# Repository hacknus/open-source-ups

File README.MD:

# Open Source UPS

[!CAUTION]
The BOOST circuit in rev 2 cannot provide sufficient current to start a HDD.

UPS are commonly used in server applications to protect against power outages. For home applications, for example to protect a NAS, small Uninterruptible Power Supplies (UPS) do exist, but they all lack the USB HID communication to shut down the NAS/Server/Host when the battery gets low.
For small scale applications like Synology NAS products that operate at 12V, there currently exists no UPS product that is able to buffer the power and communicate over USB when the battery level gets critically low.
Only high voltage solutions (110V or 230V) exist, which also include an inverter and are thus much less efficient and overpowered for a simple 12V Synology NAS.
This is a simple, open source UPS, based around an STM32F405 and written in Rust.

The USB HID communication is based on the great work done by [abratchik](https://github.com/abratchik) for the Arduino platform [here](https://github.com/abratchik/HIDPowerDevice/tree/master). 
The hardware is essentially just a charging circuit where the remaining capacity is monitored by the MCU.

## Hardware
Attention! This pcb does not contain a battery protection circuit - if you wish to implement one, just use the Keystone 1047 battery case instead of the Keystone 1048P and wire a breakout 2S BMS before connecting the batteries to the PCB.
The hardware can be found in the [hardware folder](hardware), containing step files for the case as well as EAGLE files for the PCB.

## Flashing the firmware
Easiest way to flash: Connect via USB-C to your computer. Press RESET and BOOT button on the back of the PCB, release RST first and then release BOOT. The device is now in DFU mode.

Then run the following:
```sh
cargo build --release
/usr/bin/arm-none-eabi-objcopy -O binary   target/thumbv7em-none-eabihf/release/open-source-ups   firmware.bin
dfu-util -l
dfu-util -d 0483:df11 -a 0 \
  -s 0x08000000:leave -D firmware.bin
```

Alternatively:
Connect the board using a ST-Link V3 (with TagConnect) to a USB port on the computer. Be sure to power the board with an
additional USB-C connector. (ST-Link does not provide power)  
First start the openocd server in a terminal/console window:
```openocd -f interface/stlink-v2-1.cfg -f target/stm32f4x.cfg```   
Flash/Run the code on the hardware using:  
```cargo run --release```  
note: release is important for USB to work reliably!

To set up your system, be sure to
follow [this guide](https://docs.rust-embedded.org/discovery/f3discovery/03-setup/index.html)!

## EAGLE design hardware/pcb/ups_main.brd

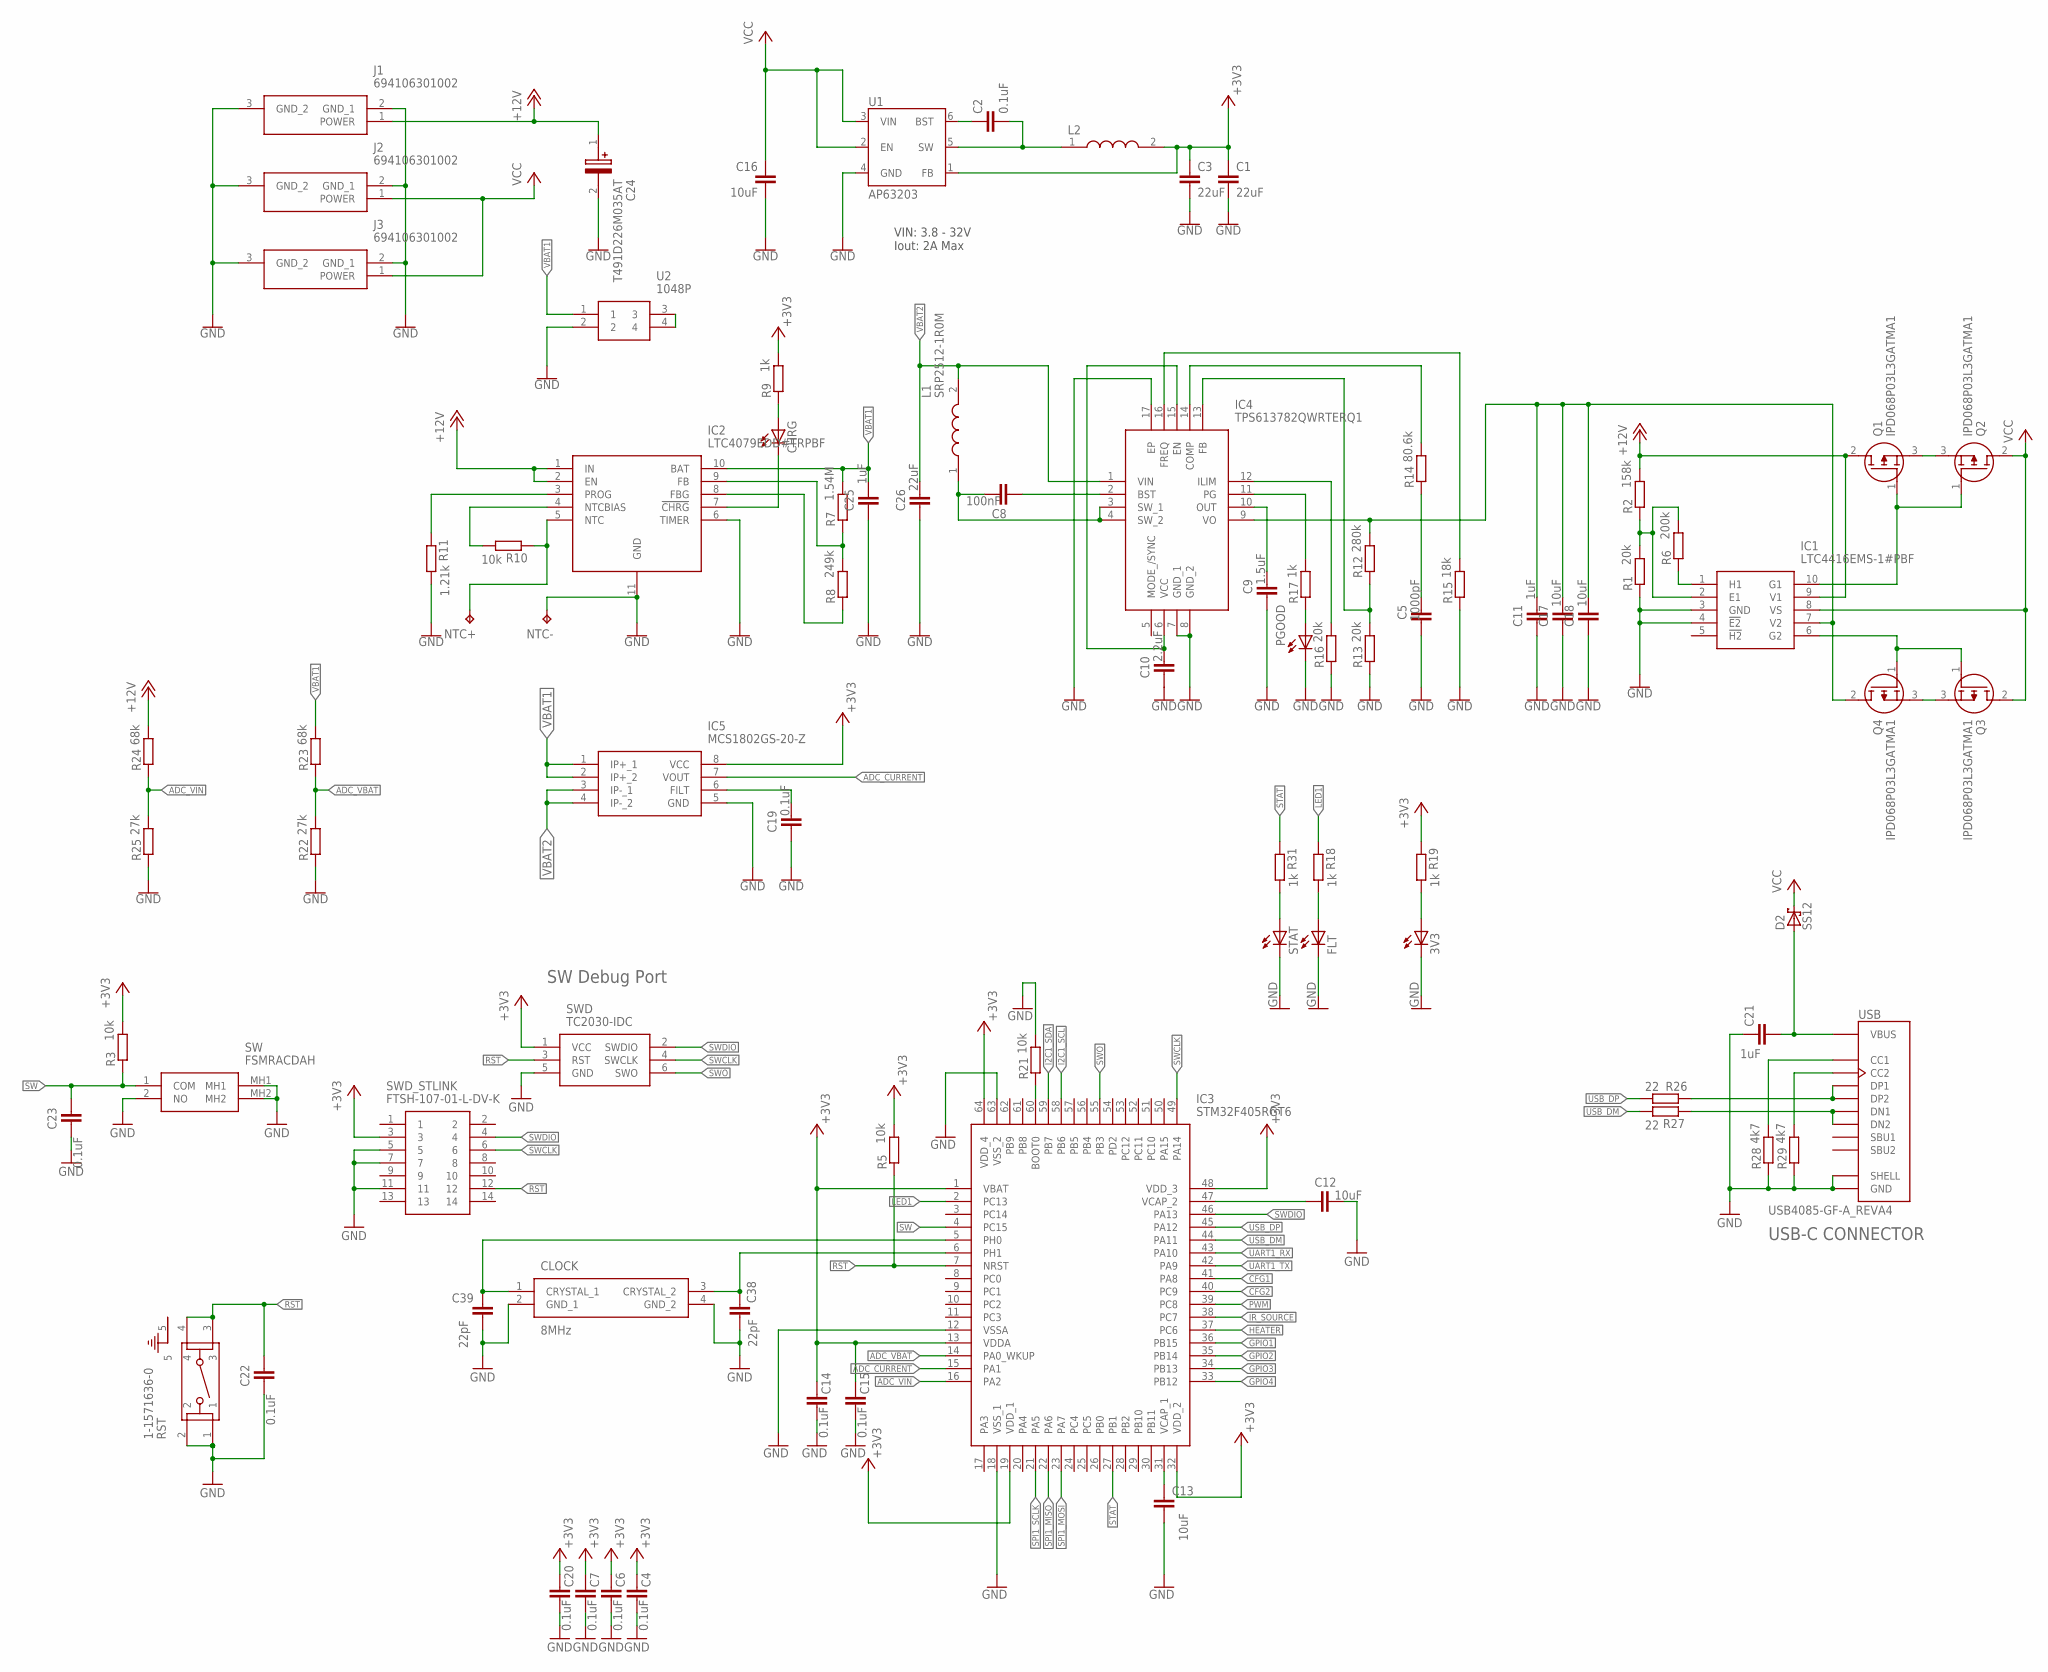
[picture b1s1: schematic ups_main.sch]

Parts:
3V3: LEDCHIPLED_0805; CHIPLED_0805
C1, C3: 22uF; 0603
C2: 0.1uF; 0603
C4, C6, C7, C14, C15, C19, C20, C22, C23: 0.1uF; C0603K
C5: 1000pF; C0603K
C8: 100nF; C0603K
C9: 1.5uF; C0603K
C10: 2.2uF; C0603K
C11, C21, C25: 1uF; C0603K
C12, C13, C17, C18: 10uF; C0603K
C16: 10uF; 1210
C24: T491D226M035AT; T491D
C26: 22uF; C0603K
C38, C39: 22pF; C0603K
CHRG: LEDCHIPLED_0805; CHIPLED_0805
CLOCK: 8MHz; ABM8AIG8000MHZ1ZT
D2: SS12; DO214AC
FLT: LEDCHIPLED_0805; CHIPLED_0805
IC1: LTC4416EMS-1#PBF; SOP50P490X110-10N
IC2: LTC4079EDD#TRPBF; SON50P300X300X80-11N
IC3: STM32F405RGT6; QFP50P1200X1200X160-64N
IC4: TPS613782QWRTERQ1; QFN50P300X300X80-17N
IC5: MCS1802GS-20-Z; SOIC127P600X175-8N
J1, J2, J3: 694106301002; 694106301002_1
L1: SRP2512-1R0M; INDC2520X120N
L2: MLZ2012M4R7HT000; INDC2012X145N
NTC+: TPPAD1-17; P1-17
NTC-: TPPAD1-17; P1-17
PGOOD: LEDCHIPLED_0805; CHIPLED_0805
Q1, Q2, Q3, Q4: IPD068P03L3GATMA1
R1, R13, R16: 20k; R0603
R2: 158k; R0603
R3, R5, R10, R21: 10k; R0603
R6: 200k; R0603
R7: 1.54M; R0603
R8: 249k; R0603
R9, R17, R18, R19, R31: 1k; R0603
R11: 1.21k; R0603
R12: 280k; R0603
R14: 80.6k; R0603
R15: 18k; R0603
R22, R25: 27k; R0603
R23, R24: 68k; R0603
R26, R27: 22; R0603
R28, R29: 4k7; R0603
RST: 1-1571636-0; SW5_1571636
STAT: LEDCHIPLED_0805; CHIPLED_0805
SW: FSMRACDAH
SWD: TC2030-IDC; TC2030IDC
SWD_STLINK: FTSH-107-01-L-DV-K; FTSH-107-XX-YYY-DV-K
U1: AP63203; SOT23-6
U2: 1048P
USB: USB4085-GF-A_REVA4; GCT_USB4085-GF-A_REVA4

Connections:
+3V3: C1.1, C3.1, C4.1, C6.1, C7.1, C14.1, C15.1, C20.1, IC3.1 (VBAT), IC3.13 (VDDA), IC3.19 (VDD_1), IC3.32 (VDD_2), IC3.48 (VDD_3), IC3.64 (VDD_4), IC5.8 (VCC), L2.2, R3.2, R5.2, R9.2, R19.1, SWD.1 (VCC), SWD_STLINK.3, U1.1 (FB)
+12V: C24.1 (+), IC1.9 (V1), IC2.1 (IN), IC2.2 (EN), J1.1 (POWER), Q1.2 (D), R2.2, R24.2
ADC_CURRENT: IC3.15 (PA1), IC5.7 (VOUT)
ADC_VBAT: IC3.14 (PA0_WKUP), R22.2, R23.1
ADC_VIN: IC3.16 (PA2), R24.1, R25.2
CFG1: IC3.41 (PA8)
CFG2: IC3.40 (PC9)
GND: 3V3.C, C1.2, C3.2, C4.2, C5.1, C6.2, C7.2, C9.1, C10.1, C11.1, C12.2, C13.2, C14.2, C15.2, C16.2, C17.1, C18.1, C19.1, C20.2, C21.1, C22.2, C23.2, C24.2 (-), C25.1, C26.1, C38.2, C39.2, CLOCK.2 (GND_1), CLOCK.4 (GND_2), FLT.C, IC1.3 (GND), IC1.4 (!E2), IC2.6 (TIMER), IC2.11 (GND), IC3.12 (VSSA), IC3.18 (VSS_1), IC3.63 (VSS_2), IC4.7 (GND_1), IC4.8 (GND_2), IC4.17 (EP), IC5.5 (GND), J1.2 (GND_1), J1.3 (GND_2), J2.2 (GND_1), J2.3 (GND_2), J3.2 (GND_1), J3.3 (GND_2), NTC-.TP, PGOOD.C, R1.1, R11.2, R13.1, R15.1, R16.1, R21.2, R22.1, R25.1, R28.1, R29.1, RST.1, RST.2, STAT.C, SW.2 (NO), SW.MH1, SW.MH2, SWD.5 (GND), SWD_STLINK.5, SWD_STLINK.7, SWD_STLINK.11, U1.4 (GND), U2.2, USB.A1 (GND), USB.A12 (GND), USB.B1 (GND), USB.B12 (GND), USB.P1 (SHELL), USB.P2 (SHELL), USB.P3 (SHELL), USB.P4 (SHELL)
GPIO1: IC3.36 (PB15)
GPIO2: IC3.35 (PB14)
GPIO3: IC3.34 (PB13)
GPIO4: IC3.33 (PB12)
HEATER: IC3.37 (PC6)
I2C1_SCL: IC3.58 (PB6)
I2C1_SDA: IC3.59 (PB7)
IR_SOURCE: IC3.38 (PC7)
LED1: IC3.2 (PC13), R18.1
unnamed: C2.1, U1.6 (BST)
unnamed: Q3.3 (S), Q4.3 (S)
unnamed: IC1.6 (G2), Q3.1 (G), Q4.1 (G)
unnamed: FLT.A, R18.2
unnamed: IC1.10 (G1), Q1.1 (G), Q2.1 (G)
unnamed: C12.1, IC3.47 (VCAP_2)
unnamed: IC1.1 (H1), R6.1
unnamed: IC1.2 (E1), R1.2, R2.1, R6.2
unnamed: C2.2, L2.1, U1.5 (SW)
unnamed: Q1.3 (S), Q2.3 (S)
unnamed: IC4.12 (ILIM), R16.2
unnamed: C13.1, IC3.31 (VCAP_1)
unnamed: IC4.11 (PG), R17.2
unnamed: IC2.4 (NTCBIAS), R10.2
unnamed: IC2.5 (NTC), NTC+.TP, R10.1
unnamed: IC2.3 (PROG), R11.1
unnamed: IC2.9 (FB), R7.1, R8.2
unnamed: IC2.8 (FBG), R8.1
unnamed: CHRG.C, IC2.7 (!CHRG)
unnamed: C38.1, CLOCK.3 (CRYSTAL_2), IC3.6 (PH1)
unnamed: C9.2, IC4.10 (OUT)
unnamed: IC4.16 (FREQ), R15.2
unnamed: IC4.14 (COMP), R14.2
unnamed: C8.1, IC4.2 (BST)
unnamed: C8.2, IC4.3 (SW_1), IC4.4 (SW_2), L1.1
unnamed: C39.1, CLOCK.1 (CRYSTAL_1), IC3.5 (PH0)
unnamed: C5.2, R14.1
unnamed: IC4.13 (FB), R12.1, R13.2
unnamed: 3V3.A, R19.2
unnamed: R31.2, STAT.A
unnamed: C21.2, D2.A, USB.A4 (VBUS), USB.A9 (VBUS), USB.B4 (VBUS), USB.B9 (VBUS)
unnamed: PGOOD.A, R17.1
unnamed: CHRG.A, R9.1
unnamed: IC3.60 (BOOT0), R21.1
unnamed: R26.1, USB.A6 (DP1), USB.B6 (DP2)
unnamed: C10.2, IC4.6 (VCC), IC4.15 (EN)
unnamed: R27.1, USB.A7 (DN1), USB.B7 (DN2)
unnamed: C19.2, IC5.6 (FILT)
unnamed: U2.3, U2.4
unnamed: R29.2, USB.B5 (CC2)
unnamed: R28.2, USB.A5 (CC1)
PWM: IC3.39 (PC8)
RST: C22.1, IC3.7 (NRST), R5.1, RST.3, RST.4, SWD.3 (RST), SWD_STLINK.12
SPI1_MISO: IC3.22 (PA6)
SPI1_MOSI: IC3.23 (PA7)
SPI1_SCLK: IC3.21 (PA5)
STAT: IC3.27 (PB1), R31.1
SW: C23.1, IC3.4 (PC15), R3.1, SW.1 (COM)
SWCLK: IC3.49 (PA14), SWD.4 (SWCLK), SWD_STLINK.6
SWDIO: IC3.46 (PA13), SWD.2 (SWDIO), SWD_STLINK.4
SWO: IC3.55 (PB3), SWD.6 (SWO)
UART1_RX: IC3.43 (PA10)
UART1_TX: IC3.42 (PA9)
USB_DM: IC3.44 (PA11), R27.2
USB_DP: IC3.45 (PA12), R26.2
VBAT1: C25.2, IC2.10 (BAT), IC5.1 (IP+_1), IC5.2 (IP+_2), R7.2, R23.2, U2.1
VBAT2: C26.2, IC4.1 (VIN), IC5.3 (IP-_1), IC5.4 (IP-_2), L1.2
VCC: C16.1, D2.C, IC1.8 (VS), J2.1 (POWER), J3.1 (POWER), Q2.2 (D), Q3.2 (D), U1.2 (EN), U1.3 (VIN)
VO: C11.2, C17.2, C18.2, IC1.7 (V2), IC4.9 (VO), Q4.2 (D), R12.2

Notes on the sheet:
SW Debug Port
VIN: 3.8 - 32V Iout: 2A Max
USB-C CONNECTOR

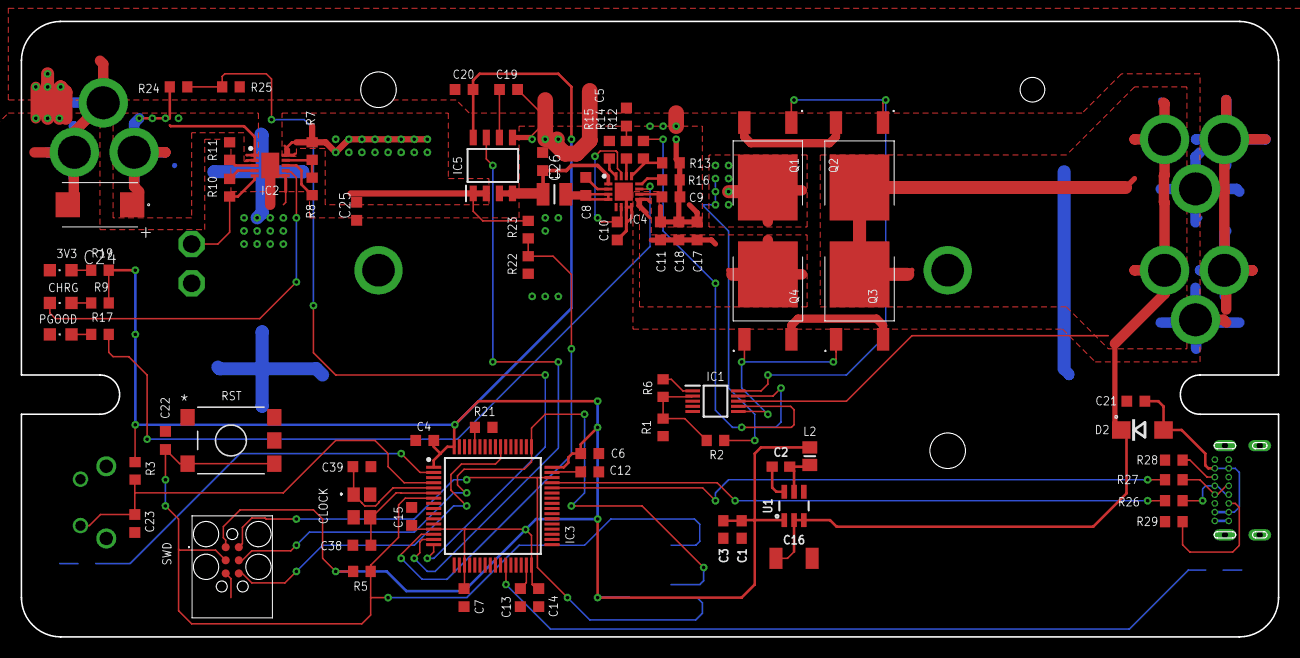
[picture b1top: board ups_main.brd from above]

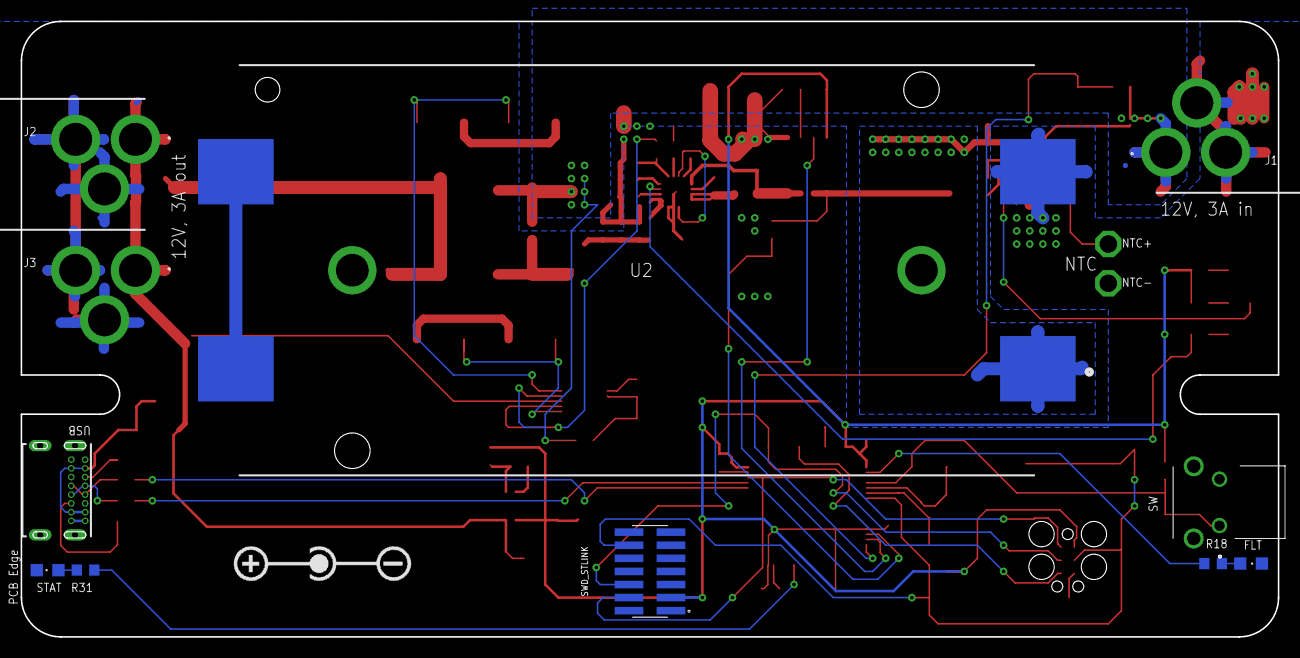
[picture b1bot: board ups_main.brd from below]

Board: 2 copper layers, 121.9 x 59.7 mm, 86 parts (11 on the bottom side), 60 nets.

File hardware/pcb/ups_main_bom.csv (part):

Qty,Value,Device,Package,Parts,Description,ARROW_PART_NUMBER,ARROW_PRICE-STOCK,AVAILABILITY,BUILT_BY,CONFIGURATION__POLE-THROW_,COPYRIGHT,DESCRIPTION,HEIGHT,MANUFACTURER_NAME,MANUFACTURER_PART_NUMBER,MAX_SWITCHING_CURRENT,MAX_SWITCHING_VOLTAGE_AC_,MF,MOUSER_PART_NUMBER,MOUSER_PRICE-STOCK,MP,PACKAGE,POPULARITY,PRICE,PRODUCT_TYPE,PROD_ID,PURCHASE-URL,RS_PART_NUMBER,RS_PRICE-STOCK,SPICEPREFIX,SWITCH_TYPE,TE_PART_NUMBER,TP_SIGNAL_NAME,VALUE,VENDOR,
5,,LEDCHIPLED_0805,CHIPLED_0805,"3V3, CHRG, FLT, PGOOD, STAT",LED,,,,,,,,,,,,,,,,,,,,,,,,,,,,,,,
1,0.1uF,0.1UF-0603-25V-5%,603,C2,0.1µF ceramic capacitors,,,,,,,,,,,,,,,,,,,,,CAP-08604,,,,,,,,0.1uF,,
9,0.1uF,C-EUC0603K,C0603K,"C4, C6, C7, C14, C15, C19, C20, C22, C23","CAPACITOR, European symbol",,,,,,,,,,,,,,,,,,30,,,,,,,C,,,,,,
1,1-1571636-0,1-1571636-0,SW5_1571636,RST,,,,,EMA_UL_Team,Single Pole - Single Throw,Copyright (C) 2016 Accelerated Designs. All rights reserved,"TACT,SMT,GULL WING,260GF,T&R",,,1-1571636-0,-,-,,,,,,,,Switch,,,,,,Tactile Switches,1-1571636-0,,,TE Connectivity,
1,1.21k,R-EU_R0603,R0603,R11,"RESISTOR, European symbol",,,,,,,,,,,,,,,,,,70,,,,,,,R,,,,,,
1,1.54M,R-EU_R0603,R0603,R7,"RESISTOR, European symbol",,,,,,,,,,,,,,,,,,70,,,,,,,R,,,,,,
1,1.5uF,C-EUC0603K,C0603K,C9,"CAPACITOR, European symbol",,,,,,,,,,,,,,,,,,30,,,,,,,C,,,,,,
1,1000pF,C-EUC0603K,C0603K,C5,"CAPACITOR, European symbol",,,,,,,,,,,,,,,,,,30,,,,,,,C,,,,,,
1,100nF,C-EUC0603K,C0603K,C8,"CAPACITOR, European symbol",,,,,,,,,,,,,,,,,,30,,,,,,,C,,,,,,
1,1048P,1048P,1048P,U2,"KEYSTONE - 1048P - BATTERY HOLDER, 18650, SMD",,,,,,,"KEYSTONE - 1048P - BATTERY HOLDER, 18650, SMD",mm,Keystone Electronics,1048P,,,,534-1048P,https://www.mouser.co.uk/ProductDetail/Keystone-Electronics/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,,,,,,,,,,,,,,,,
4,10k,R-EU_R0603,R0603,"R3, R5, R10, R21","RESISTOR, European symbol",,,,,,,,,,,,,,,,,,70,,,,,,,R,,,,,,
1,10uF,10UF-1210-50V-20%,1210,C16,10.0µF ceramic capacitors,,,,,,,,,,,,,,,,,,,,,CAP-09824,,,,,,,,10uF,,
4,10uF,C-EUC0603K,C0603K,"C12, C13, C17, C18","CAPACITOR, European symbol",,,,,,,,,,,,,,,,,,30,,,,,,,C,,,,,,
1,158k,R-EU_R0603,R0603,R2,"RESISTOR, European symbol",,,,,,,,,,,,,,,,,,70,,,,,,,R,,,,,,
1,18k,R-EU_R0603,R0603,R15,"RESISTOR, European symbol",,,,,,,,,,,,,,,,,,70,,,,,,,R,,,,,,
5,1k,R-EU_R0603,R0603,"R9, R17, R18, R19, R31","RESISTOR, European symbol",,,,,,,,,,,,,,,,,,70,,,,,,,R,,,,,,
3,1uF,C-EUC0603K,C0603K,"C11, C21, C25","CAPACITOR, European symbol",,,,,,,,,,,,,,,,,,30,,,,,,,C,,,,,,
1,2.2uF,C-EUC0603K,C0603K,C10,"CAPACITOR, European symbol",,,,,,,,,,,,,,,,,,30,,,,,,,C,,,,,,
1,200k,R-EU_R0603,R0603,R6,"RESISTOR, European symbol",,,,,,,,,,,,,,,,,,70,,,,,,,R,,,,,,
3,20k,R-EU_R0603,R0603,"R1, R13, R16","RESISTOR, European symbol",,,,,,,,,,,,,,,,,,70,,,,,,,R,,,,,,
2,22,R-EU_R0603,R0603,"R26, R27","RESISTOR, European symbol",,,,,,,,,,,,,,,,,,70,,,,,,,R,,,,,,
2,22pF,C-EUC0603K,C0603K,"C38, C39","CAPACITOR, European symbol",,,,,,,,,,,,,,,,,,30,,,,,,,C,,,,,,
2,22uF,22UF-0603-6.3V-20%,603,"C1, C3",22µF ceramic capacitors,,,,,,,,,,,,,,,,,,,,,CAP-14464,,,,,,,,22uF,,
1,22uF,C-EUC0603K,C0603K,C26,"CAPACITOR, European symbol",,,,,,,,,,,,,,,,,,30,,,,,,,C,,,,,,
1,249k,R-EU_R0603,R0603,R8,"RESISTOR, European symbol",,,,,,,,,,,,,,,,,,70,,,,,,,R,,,,,,
2,27k,R-EU_R0603,R0603,"R22, R25","RESISTOR, European symbol",,,,,,,,,,,,,,,,,,70,,,,,,,R,,,,,,
1,280k,R-EU_R0603,R0603,R12,"RESISTOR, European symbol",,,,,,,,,,,,,,,,,,70,,,,,,,R,,,,,,
2,4k7,R-EU_R0603,R0603,"R28, R29","RESISTOR, European symbol",,,,,,,,,,,,,,,,,,70,,,,,,,R,,,,,,
2,68k,R-EU_R0603,R0603,"R23, R24","RESISTOR, European symbol",,,,,,,,,,,,,,,,,,70,,,,,,,R,,,,,,
3,694106301002,694106301002,694106301002_1,"J1, J2, J3","WURTH ELEKTRONIK - 694106301002 - CONNECTOR, POWER ENTRY, JACK, 3A, 20VDC",,,,,,,"WURTH ELEKTRONIK - 694106301002 - CONNECTOR, POWER ENTRY, JACK, 3A, 20VDC",mm,Wurth Elektronik,694106301002,,,,710-694106301002,https://www.mouser.co.uk/ProductDetail/Wurth-Elektronik/6941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,,,,,,,,,,,,,,,,
1,80.6k,R-EU_R0603,R0603,R14,"RESISTOR, European symbol",,,,,,,,,,,,,,,,,,70,,,,,,,R,,,,,,
1,8MHz,ABM8AIG-8.000MHZ-1Z-T,ABM8AIG8000MHZ1ZT,CLOCK,Crystals 18pF 8MHz 10ppm AEC-Q200 -40C +125C,,,,,,,Crystals 18pF 8MHz 10ppm AEC-Q200 -40C +125C,0.8mm,ABRACON,ABM8AIG-8.000MHZ-1Z-T,,,,815-M8AIG-8-1ZT,https://www.mouser.com/Search/Refine.aspx?Keyword=815-M8AIG-8-1ZT,,,,,,,,,,,,,,,,
1,AP63203,AP63203,SOT23-6,U1,Diodes Inc. AP63203 3.8V-32V input 3.3V Buck,,,,,,,,,,,,,,,,,,,,,VREG-15244,,,,,,,,AP63203,,
1,FSMRACDAH,FSMRACDAH,FSMRACDAH,SW,"TE CONNECTIVITY / ALCOSWITCH - FSMRACDAH - TACTILE SWITCH, SPST-NO, 0.05A, 24V, TH",,,,,,,"TE CONNECTIVITY / ALCOSWITCH - FSMRACDAH - TACTILE SWITCH, SPST-NO, 0.05A, 24V, TH",9.2mm,TE Connectivity,FSMRACDAH,,,,506-FSMRACDAH,https://www.mouser.co.uk/ProductDetail/TE-Connectivity-Alcos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,,,,,,,,,,,,,,,,
1,FTSH-107-01-L-DV-K,FTSH-107-01-L-DV-K,FTSH-107-XX-YYY-DV-K,SWD_STLINK,"14 Position, High Reliability Header Strips, 0.050 pitch""",FTSH-107-01-L-DV-K,https://www.arrow.com/en/products/ftsh-107-01-l-dv-k/samtec,,,,,"14 Position, High Reliability Header Strips, 0.050&quot", pitch,mm,SAMTEC,FTSH-107-01-L-DV-K,,,,200-FTSH10701LDVK,https://www.mouser.co.uk/ProductDetail/Samtec/FTSH-107-01-L-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,,,,,,,,,,,,,,,
4,IPD068P03L3GATMA1,IPD068P03L3GATMA1,IPD068P03L3GATMA1,"Q1, Q2, Q3, Q4",MOSFET TRENCH,,,,,,,MOSFET TRENCH <= 40V,2.41mm,Infineon,IPD068P03L3GATMA1,,,,726-IPD068P03L3GATMA,https://www.mouser.co.uk/ProductDetail/Infineon-Technologies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,,,,,,,,,,,,,,,,
1,LTC4079EDD#TRPBF,LTC4079EDD#TRPBF,SON50P300X300X80-11N,IC2,"Battery Management Low Iq 60V, 250mA Linear Charger",,,,,,,"Battery Management Low Iq 60V, 250mA Linear Charger",0.8mm,Analog Devices,LTC4079EDD#TRPBF,,,,584-LTC4079EDD#TRPBF,https://www.mouser.co.uk/ProductDetail/Analog-Devices/LTC407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,,,,,,,,,,,,,,,,
1,LTC4416EMS-1#PBF,LTC4416EMS-1#PBF,SOP50P490X110-10N,IC1,"Linear Technology LTC4416EMS-1#PBF, MOSFET Controller 10-Pin, MSOP",,,,,,,"Linear Technology LTC4416EMS-1#PBF, MOSFET Controller 10-Pin, MSOP",1.1mm,Analog Devices,LTC4416EMS-1#PBF,,,,584-LTC4416EMS-1#PBF,https://www.mouser.co.uk/ProductDetail/Analog-Devices/LTC441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,,,,,,,,,,,,,,,,
1,MCS1802GS-20-Z,MCS1802GS-20-Z,SOIC127P600X175-8N,IC5,Board Mount Current Sensors 3.3V Hall current sensor. 1.5% accuracy. 2.4kV Isolation,,,,,,,Board Mount Current Sensors 3.3V Hall current sensor. 1.5% accuracy. 2.4kV Isolation,1.75mm,Monolithic Power Systems (MPS),MCS1802GS-20-Z,,,,946-MCS1802GS-20-Z,https://www.mouser.co.uk/ProductDetail/Monolithic-Power-Syst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,,,,,,,,,,,,,,,,
1,MLZ2012M4R7HT000,MLZ2012M4R7HT000,INDC2012X145N,L2,Inductor Power Shielded Multi-Layer 4.7uH 20% 2MHz Ferrite 0.4A 0.442Ohm DCR 0805 T/R,,,,,,,Inductor Power Shielded Multi-Layer 4.7uH 20% 2MHz Ferrite 0.4A 0.442Ohm DCR 0805 T/R,1.45mm,TDK-Lambda,MLZ2012M4R7HT000,,,,810-MLZ2012M4R7HT000,https://www.mouser.co.uk/ProductDetail/TDK/MLZ2012M4R7HT000?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,,,,,,,,,,,,,,,,
1,SRP2512-1R0M,SRP2512-1R0M,INDC2520X120N,L1,"BOURNS - SRP2512-1R0M - INDUCTOR, WIREWOUND, 1UH, 20%, 3.1A",,,,,,,"BOURNS - SRP2512-1R0M - INDUCTOR, WIREWOUND, 1UH, 20%, 3.1A",1.2mm,Bourns,SRP2512-1R0M,,,,652-SRP2512-1R0M,https://www.mouser.co.uk/ProductDetail/Bourns/SRP2512-1R0M?q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,,,,,,,,,,,,,,,,
1,SS12,SS12,DO214AC,D2,http://octopart.com/ss12-tp-mcc-9293796,,,Unavailable,,,,SS12 Series 500 mV 1 A 20 V Max Reverse Voltage Schottky Rectifier - DO-214AC,,,,,,"Klein Tools,",,,SS12,DO-214AC-214 ON Semiconductor,,None,,,,,,,,,,,,
1,STM32F405RGT6,STM32F405RGT6,QFP50P1200X1200X160-64N,IC3,"MCU 32-Bit, ARM Cortex M4, 1MB Flash STMicroelectronics STM32F405RGT6, 32bit ARM Cortex M4F Microcontroller, 168MHz, 1024 kB Flash, 64-Pin LQFP",,,,,,,"MCU 32-Bit, ARM Cortex M4, 1MB Flash STMicroelectronics STM32F405RGT6, 32bit ARM Cortex M4F Microcontroller, 168MHz, 1024 kB Flash, 64-Pin LQFP",1.6mm,STMicroelectronics,STM32F405RGT6,,,,511-STM32F405RGT6,https://www.mouser.co.uk/ProductDetail/STMicroelectronics/ST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,,,,,,,,,,,,,,,,
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
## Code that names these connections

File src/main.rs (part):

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    let valid1 = gpiob.pb12.into_floating_input();
    let valid2 = gpiob.pb13.into_floating_input();

    // U7 PB1 (pin 27): STAT, TIM3 channel 4.
    let led_dim = Channel4::new(gpiob.pb1);

    // U7 PC13 (pin 2): LED1.
    let mut usb_led1 = LED::new(gpioc.pc13.into_push_pull_output());

    // initialize pwm timer 3
    let mut stat_led_pwm = dp.TIM3.pwm_hz(led_dim, 10000.Hz(), &clocks).split();

    // U7 PA0/PA1/PA2 (pins 14/15/16): ADC_VBAT/ADC_CURRENT/ADC_VIN.

    let adc_vbat = gpioa.pa0.into_analog();
    let adc_current = gpioa.pa1.into_analog();
    let adc_vin = gpioa.pa2.into_analog();

    let dma_config = DmaConfig::default()
        .transfer_complete_interrupt(true)
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    }
    adc::start_scan();

    // U7 PC15 (pin 4): SW; the board provides the external pull-up.
    let sw = gpioc.pc15.into_floating_input();
    // U7 PA11/PA12 (pins 44/45): USB_DM/USB_DP.
    let usb = USB {
        usb_global: dp.OTG_FS_GLOBAL,
        usb_device: dp.OTG_FS_DEVICE,
        usb_pwrclk: dp.OTG_FS_PWRCLK,
        pin_dm: stm32f4xx_hal::gpio::alt::otg_fs::Dm::PA11(gpioa.pa11.into_alternate()),
        pin_dp: stm32f4xx_hal::gpio::alt::otg_fs::Dp::PA12(gpioa.pa12.into_alternate()),
        hclk: clocks.hclk(),
    };
    delay.delay(100.millis());
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
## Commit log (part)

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2024-08-11 test USB HID
2024-08-12 HID usb.rs
2024-08-12 change vid/pid and descriptor
2024-08-12 testing battery level reporting
2024-08-12 delay out of loop
2024-08-12 change delay
2024-08-12 capacity to u8
2024-08-12 try this
2024-08-12 struct
2024-08-12 long descriptor
2024-08-13 reporting in usb interrupt
2024-08-13 use different library
2024-08-14 send more information in report
2024-08-14 increase report count
2024-08-14 undo report size change
2024-08-14 send three reports
2024-08-14 this somehow did shut down the NAS
2024-08-14 use bitfields
2024-08-14 cleanup
2024-08-14 set status variables
2024-08-14 working UPS with synology
2024-08-14 fix reports
2024-08-14 include dummy logic
2024-09-27 add hardware files
2024-09-30 implemented IO pins
2024-09-30 slow sine for LED implemented
2024-10-01 update schem
2024-10-01 change name of USB dev
2024-10-01 add BMS note
2024-10-26 fix errors in schem/layout
2024-10-27 fix pgood led
2024-10-28 change led blink speed when power supply is disconnected
2024-10-28 fix adc
2024-10-28 fix voltage reading
2024-10-28 switch battery and ac present flags
2024-10-29 implement usb serial for debugging
2024-10-29 include usb interrupt for serial
2024-10-30 no charging might trigger shutdown
2024-10-30 minutes to seconds
2024-10-30 working version with synology
2026-04-29 Update README with caution about PCB design error
    Added caution note about PCB design error.

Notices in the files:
parts and their libraries:
SparkFun-Capacitors: Licensing: Creative Commons ShareAlike 4.0 International - https://creativecommons.org/licenses/by-sa/4.0
COPYRIGHT: Copyright (C) 2016 Accelerated Designs. All rights reserved
